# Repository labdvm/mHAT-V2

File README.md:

# mHAT-V2
SX1255 TMO mini-HAT with BPF

- SAW Bandpass filters:
- RX, TA0665A (https://www.aliexpress.com/item/1005011831789075.html?pdp_ext_f=%7B%22sku_id%22%3A%2212000056730460079%22%7D&sourceType=1&spm=a2g0o.wish-manage-home.0.0)
- TX, TA2490A (https://www.aliexpress.com/item/1005011831747244.html?pdp_ext_f=%7B%22sku_id%22%3A%2212000056722939672%22%7D&sourceType=1&spm=a2g0o.wish-manage-home.0.0)

# Order from here:
-

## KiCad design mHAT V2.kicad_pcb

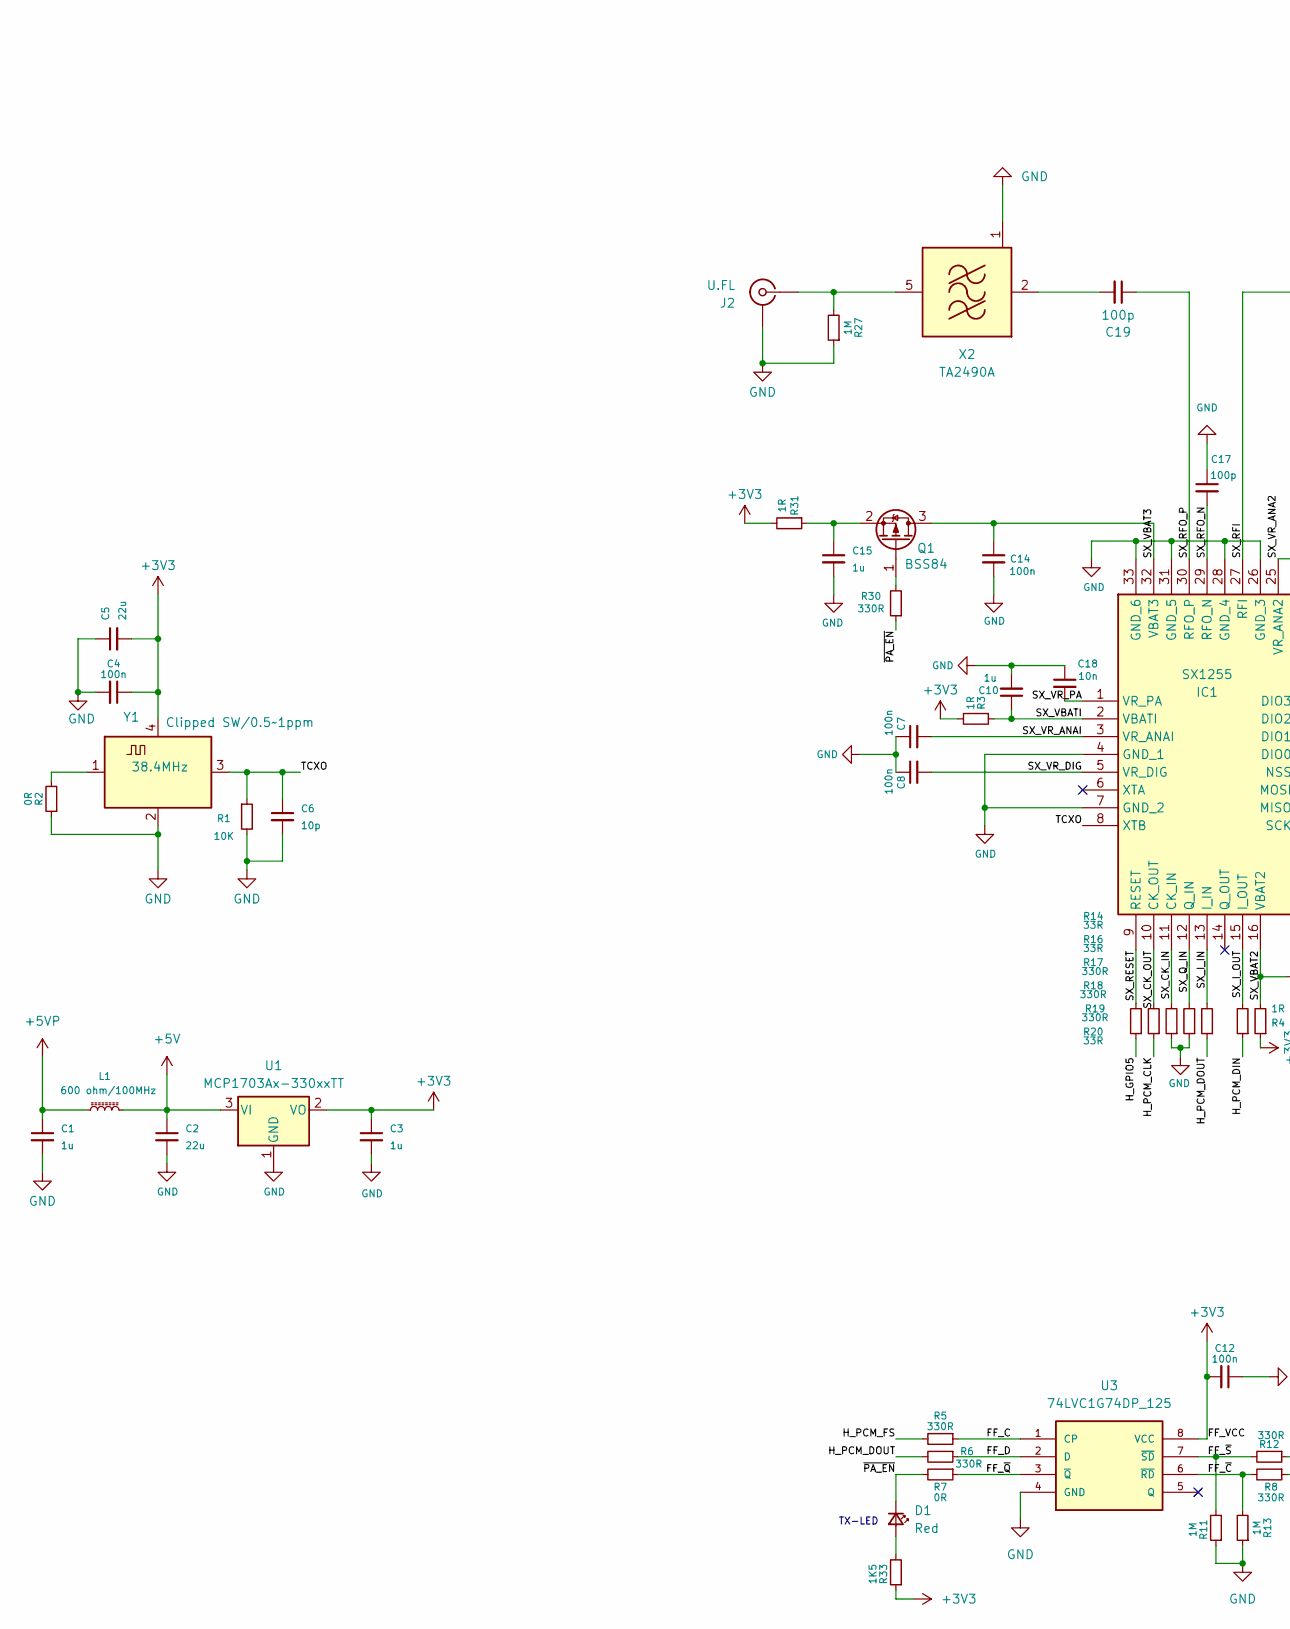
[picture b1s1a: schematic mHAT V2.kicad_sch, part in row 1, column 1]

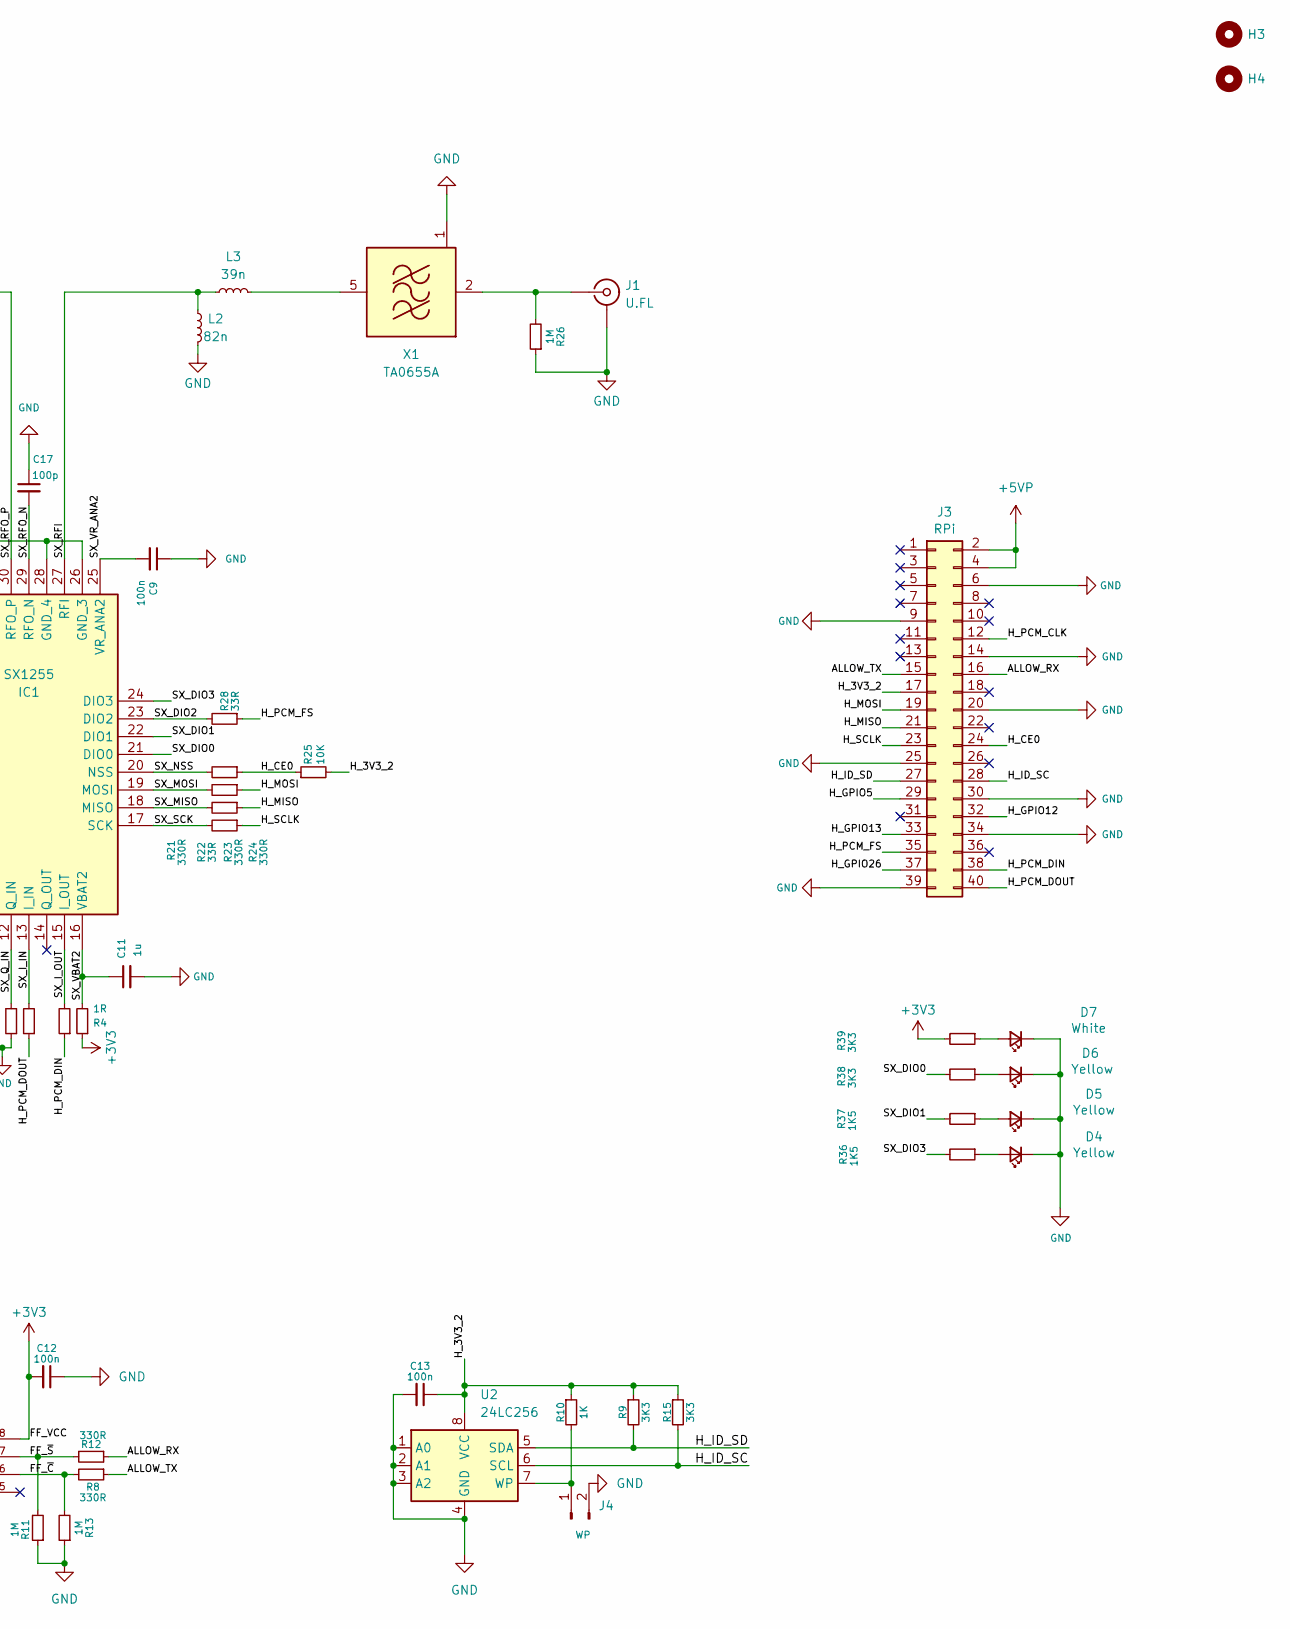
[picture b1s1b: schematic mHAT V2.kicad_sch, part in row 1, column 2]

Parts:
C1, C3, C10, C11, C15: 1u; C_0603_1608Metric; Part Number 311-3484-1-ND
C2, C5: 22u; C_0805_2012Metric; Part Number 1276-2910-1-ND
C4, C9, C12, C13, C14: 100n; C_0603_1608Metric; Part Number 720-1688-1-ND
C6: 10p; C_0603_1608Metric; Part Number 399-14932-1-ND
C7, C8: 100n; C_0402_1005Metric_Pad0.74x0.62mm_HandSolder; Part Number 490-10777-1-ND
C17, C19: 100p; C_0603_1608Metric; Part Number 478-KGM15ACG1H101FTCT-ND
C18: 10n; C_0402_1005Metric_Pad0.74x0.62mm_HandSolder; Part Number 399-C0402C102J8HACAUTOCT-ND
D1: Red; LED_0603_1608Metric_Pad1.05x0.95mm_HandSolder; Part Number 160-1436-1-ND
D4, D5, D6: Yellow; LED_0603_1608Metric_Pad1.05x0.95mm_HandSolder; Part Number 160-1437-1-ND
D7: White; LED_0603_1608Metric_Pad1.05x0.95mm_HandSolder; Part Number 160-1724-1-ND
H3, H4: MountingHole; MountingHole_2.7mm_M2.5_DIN965
IC1: SX1255; QFN-32-1EP_5x5mm_P0.5mm_EP3.3x3.3mm_ThermalVias; Part Number SX1255IWLTRTCT-ND
J1, J2: U.FL; Part Number 343-CONMHF1-SMD-G-TCT-ND
J3: RPi; PinSocket_2x20_P2.54mm_Vertical
J4: WP; PinHeader_1x02_P2.54mm_Vertical
L1: 600 ohm/100MHz; L_0603_1608Metric; Part Number 490-1046-1-ND
L2: 82n; L_0603_1608Metric; Part Number 712-LRC0603CJ82NGV001TCT-ND
L3: 39n; L_0603_1608Metric; Part Number 712-LRC0603CJ39NGV001TCT-ND
Q1: BSS84; SOT-23; Part Number 3372-BSS84TR-ND
R1, R25: 10K; R_0603_1608Metric; Part Number 541-10.0KHCT-ND
R2: 0R; R_0603_1608Metric; Part Number 541-0.0GCT-ND
R3, R4: 1R; R_0402_1005Metric_Pad0.72x0.64mm_HandSolder; Part Number 541-RCC04021R00FKEDCT-ND
R5, R6, R8, R12, R17, R18, R21, R23, R24: 330R; R_0402_1005Metric_Pad0.72x0.64mm_HandSolder; Part Number 13-AC0402FR-7W330RLCT-ND
R7: 0R; R_0402_1005Metric_Pad0.72x0.64mm_HandSolder; Part Number 541-0.0JCT-ND
R9, R15: 3K3; R_0402_1005Metric_Pad0.72x0.64mm_HandSolder; Part Number 541-RCC04023K30FKEDCT-ND
R10: 1K; R_0402_1005Metric_Pad0.72x0.64mm_HandSolder; Part Number 13-RC0402FR-7W1KLCT-ND
R11, R13: 1M; R_0402_1005Metric_Pad0.72x0.64mm_HandSolder; Part Number 311-1.00MLRCT-ND
R14, R16, R20, R22, R28: 33R; R_0402_1005Metric_Pad0.72x0.64mm_HandSolder; Part Number 13-AC0402FR-7W33RLCT-ND
R19: 330R; R_0603_1608Metric; Part Number 13-AC0402FR-7W330RLCT-ND
R26, R27: 1M; R_0603_1608Metric; Part Number 541-1.00MHCT-ND
R30: 330R; R_0603_1608Metric; Part Number 541-330HCT-ND
R31: 1R; R_0603_1608Metric; Part Number 541-1.00HHCT-ND
R33, R36, R37: 1K5; R_0603_1608Metric; Part Number 541-1.50KHCT-ND
R38, R39: 3K3; R_0603_1608Metric; Part Number 541-3.30KHCT-ND
U1: MCP1703Ax-330xxTT; SOT-23; Part Number MCP1703AT-3302E/CBCT-ND
U2: 24LC256; SOIC-8_3.9x4.9mm_P1.27mm; Part Number 24LC256-I/SN-ND
U3: 74LVC1G74DP_125; SOP65P400X110-8N; Part Number 1727-5983-1-ND
X1: TA0655A; Filter_SAW-6_3.8x3.8mm; Part Number TA0655A
X2: TA2490A; Filter_SAW_Epcos_DCC6C_3x3mm; Part Number TA2490A
Y1: 38.4MHz; Crystal_SMD_3225-4Pin_3.2x2.5mm; Part Number 114-TG2520SMN38.4000M-MCGNNM3CT-ND

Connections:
+3V3: C3.1, C4.1, C5.2, C12.2, R3.2, R4.1, R31.2, R33.1, R39.2, U1.2 (VO), U3.8 (VCC), Y1.4 (VDD)
+5V: C2.1, L1.2, U1.3 (VI)
+5VP: C1.1, J3.2, J3.4, L1.1
/ALLOW_RX: J3.16, R12.1
/ALLOW_TX: J3.15, R8.1
/FF_C: R5.1, U3.1 (CP)
/FF_D: R6.1, U3.2 (D)
/FF_~C: R8.2, R13.2, U3.6 (~RD)
/FF_~Q: R7.1, U3.3 (~Q)
/FF_~S: R11.2, R12.2, U3.7 (~SD)
/H_3V3_2: C13.1, J3.17, R9.1, R10.1, R15.1, R25.2, U2.8 (VCC)
/H_CE0: J3.24, R24.1, R25.1
/H_GPIO5: J3.29, R14.1
/H_GPIO12: J3.32
/H_GPIO13: J3.33
/H_GPIO26: J3.37
/H_ID_SC: J3.28, R15.2, U2.6 (SCL)
/H_ID_SD: J3.27, R9.2, U2.5 (SDA)
/H_MISO: J3.21, R22.1
/H_MOSI: J3.19, R23.1
/H_PCM_CLK: J3.12, R16.1
/H_PCM_DIN: J3.38, R20.1
/H_PCM_DOUT: J3.40, R6.2, R19.1
/H_PCM_FS: J3.35, R5.2, R28.1
/H_SCLK: J3.23, R21.1
/SX_CK_IN: IC1.11 (CK_IN), R17.2
/SX_CK_OUT: IC1.10 (CK_OUT), R16.2
/SX_DIO0: IC1.21 (DIO0), R38.2
/SX_DIO1: IC1.22 (DIO1), R37.2
/SX_DIO2: IC1.23 (DIO2), R28.2
/SX_DIO3: IC1.24 (DIO3), R36.2
/SX_I_IN: IC1.13 (I_IN), R19.2
/SX_I_OUT: IC1.15 (I_OUT), R20.2
/SX_MISO: IC1.18 (MISO), R22.2
/SX_MOSI: IC1.19 (MOSI), R23.2
/SX_NSS: IC1.20 (NSS), R24.2
/SX_Q_IN: IC1.12 (Q_IN), R18.2
/SX_RESET: IC1.9 (RESET), R14.2
/SX_RFI: IC1.27 (RFI), L2.2, L3.2
/SX_RFO_N: C17.2, IC1.29 (RFO_N)
/SX_RFO_P: C19.1, IC1.30 (RFO_P)
/SX_SCK: IC1.17 (SCK), R21.2
/SX_VBAT2: C11.1, IC1.16 (VBAT2), R4.2
/SX_VBAT3: C14.1, IC1.32 (VBAT3), Q1.3 (D)
/SX_VBATI: C10.1, IC1.2 (VBATI), R3.1
/SX_VR_ANA2: C9.2, IC1.25 (VR_ANA2)
/SX_VR_ANAI: C7.2, IC1.3 (VR_ANAI)
/SX_VR_DIG: C8.2, IC1.5 (VR_DIG)
/SX_VR_PA: C18.2, IC1.1 (VR_PA)
/TCXO: C6.1, IC1.8 (XTB), R1.1, Y1.3 (OUT)
/~PA_EN: D1.1 (K), R7.2, R30.1
GND: C1.2, C2.2, C3.2, C4.2, C5.1, C6.2, C7.1, C8.1, C9.1, C10.2, C11.2, C12.1, C13.2, C14.2, C15.2, C17.1, C18.1, D4.1 (K), D5.1 (K), D6.1 (K), D7.1 (K), IC1.4 (GND_1), IC1.7 (GND_2), IC1.26 (GND_3), IC1.28 (GND_4), IC1.31 (GND_5), IC1.33 (GND_6), J1.2 (Ext), J2.2 (Ext), J3.6, J3.9, J3.14, J3.20, J3.25, J3.30, J3.34, J3.39, J4.2, L2.1, R1.2, R2.1, R11.1, R13.1, R17.1, R18.1, R26.1, R27.1, U1.1 (GND), U2.1 (A0), U2.2 (A1), U2.3 (A2), U2.4 (GND), U3.4 (GND), X1.1 (GND), X1.3 (GND), X1.4 (GND), X1.6 (GND), X2.1 (GND), X2.3 (GND), X2.4 (GND), X2.6 (GND), Y1.2 (GND)
unnamed: D1.2 (A), R33.2
unnamed: D4.2 (A), R36.1
unnamed: D5.2 (A), R37.1
unnamed: D6.2 (A), R38.1
unnamed: D7.2 (A), R39.1
unnamed: J1.1 (In), R26.2, X1.2 (IN)
unnamed: J2.1 (In), R27.2, X2.5 (OUT)
unnamed: J4.1, R10.2, U2.7 (WP)
unnamed: Q1.1 (G), R30.2
unnamed: C15.1, Q1.2 (S), R31.1
unnamed: L3.1, X1.5 (OUT)
unnamed: C19.2, X2.2 (IN)
unnamed: R2.2, Y1.1 (Tri-State)

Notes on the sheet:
TX-LED

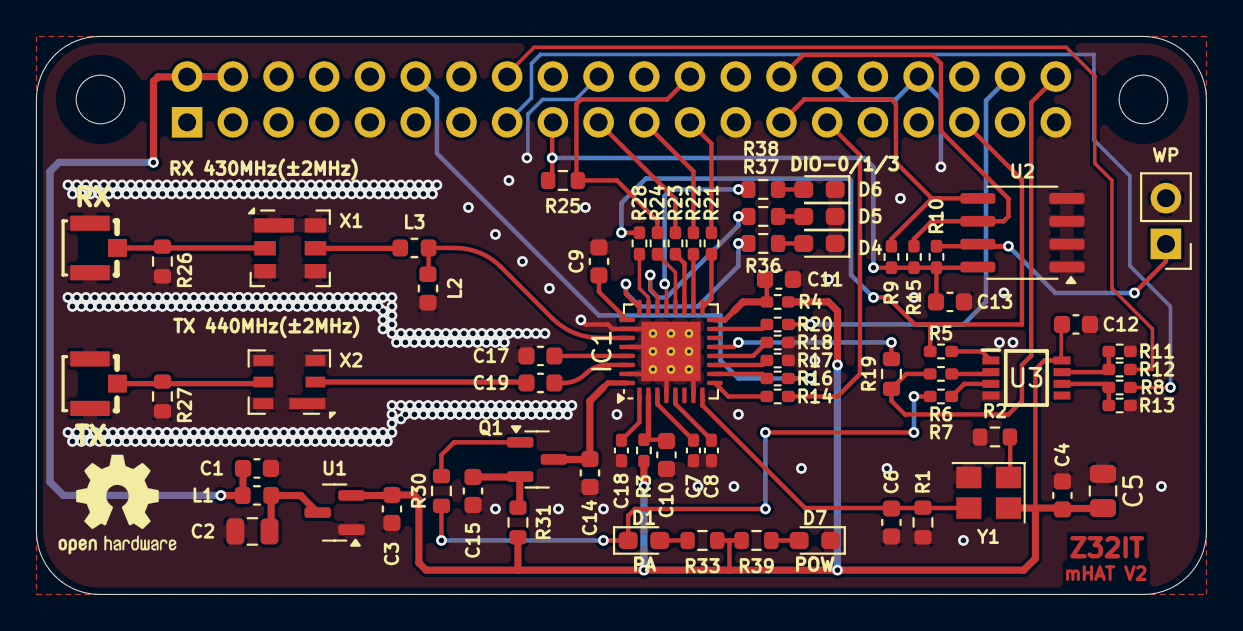
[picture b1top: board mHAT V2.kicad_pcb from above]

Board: 2 copper layers, 65.0 x 31.0 mm, 75 parts (1 on the bottom side), 62 nets.

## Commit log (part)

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2026-06-18 Add ordering information to README
    Added order link for mHAT-V2 from PCBWay.
